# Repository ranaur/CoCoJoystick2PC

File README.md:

# CoCoJoystick2PC

Make a CoCo (Color Computer) Joystick a USB device (and use in your emulator) with an Arduino Leonardo!

The idea is to use a simple and cheap Arduino Leonardo to simulate a HID Gamepad that reads from a original Color Computer Joystick.

## Bill Of Materials

The Bill Of Materials should be minimal:

* An Arduino Leonardo or Compatible
* A DIN-6 female connector to insert the joystick - or two, if you want to handle two joysticks.
* A push button (to set the calibrate mode)
* Optional: pin switches (or you can wire directly if you don't want to configure the USB behavior)

If you buy an original Leonardo, it would cost around US$ 25. But it will be much cheaper (like less than half) if you buy a compatible board with ATMEGA32U4 controller.

## Subprojects

There are some subprojects (directories with .INO files) I did to test some features. They are not part of the main project, and are here just for educational (and backup) purposes:

* CoCoDetectJoystick: detects when the Joystick is inserted and removed
* Prototype: just a first prototype to test the circuit. Not Usable.
* Prototype2: a second prototype, a working one. The debouncing is simple (just a delay(100)), has calibration, but the code is a mess. It works, and the main ideas of the project are already there.
* CoCoJoystick2USB: the main project, this one is the real one. (not yet in the repository, sorry).

Since version 0.3 the project don't use HID-Project (2.8.2) anymore (but I'm grateful for the insights and idea for implementing the HID protocol!). To add it go in the Arduino IDE menu: Tools/Manage Libraries ... Search for HID-Project and install it.

## Files on Main project

Since the second prototype, things got a little bit more complex and organized. Lets describe the main classes/modules:

CoCoJoystick2USB.ino => main project file. Quite simple, because it instantiates all the classes that handles everything that is needed. The real job is done by CoCoJoystick class.

CoCoJoystick.cpp/.h => handles one Joystick. The setup() method defines which pins will be used for reading the joystick info (X Axis, Y Axis, Button 1 and Button 2) and the offset of the calibration data. The loop() method handle the reading of the pins and the delegation to a handler function. It also handles the calibration routines (startCalibration, centerCalibration and endCalibration) and loading/saving it to EEPROM. The calibration is done in two phases. First phase it read the maximum/minimum of the analog joystick (the user should move the stick as far as he can in all directions). The second phase tests for the center. The user cam move it slightly to handle any vibration of the stick. Or leave it in the center. If the stick goes back to any place of this region it will be considered as "center". The calibration data is saved on the EEPROM in a offset address.
	The reading of values are done by two classes. The stick (analog) is read by two AxisEvent instances (one for X and one for Y). The buttons are handled by two instances of ButtonEvent class.

\*Event Classes => While they are different classes, both share the same paradigm. Run setup() to configure parameters (i.e. pin number, tolecance, EEPROM Offset of calibration data ...) on the loop() routine of the microprocessor call the on\*() classes, that will handle reading, and, if necessary, call the first parameter, that is a callback function. Also, the on\*() methods can receive one pointer to pass to the callback function (Normally the event object itself, but it ca be anything), and the timer (optional). The timer parameter exist to call mills() just once and reuse the value through many calls in the loop() routine. Best use example is CoCoJoystick::loop().

AxisEvent.cpp/.h => Handles on axis. Reads the pin (0 to 1023) and normalize taking account of the calibration values. Handles the calibration state, aswell. The method onChanged() fires the callback if the value read from the sensor differs for more than the "tolerance" parameter. It handles the calibration routine aswell.

ButtonEvent.cpp/.h => Handles one button, with debounce. Has methods onPressed, onReleased, onPressedFor, onReleasedFor that calls the callback function on a button press (KEYDOWN), on a button release (KEYUP), after forMs miliseconds of the button press, and the same for the releade

Calibration.cpp/.h => the Calibration Objects encapsulates the real access to EEPROM, and the mapping from real values to adjusted (calibrated) values.

CoCoGamepadConfig.h => Abstract class that represents the interface of the events that can happen with a CoCo Gamepad could do. (press and release of the buttons, axis change).

# Usage

## Calibrate button
If using a spare button for CALIBRATION (#define CALIBRATION 2)
* If pressed, start calibration process. See "Calibration Process".
* If pressed for 10 seconds, reset the calibration to defaults.

If not using a spare button for CALIBRATION (#define CALIBRATION 1)
During the first 60 seconds after inserting the USB connector, if the user press the red button for 5 seconds, the calibration process starts.
	While it can be calibrated, the builtin led blinks continuously.
	When the calibration starts, it blinks once per second and gather the extremes.
	When you press the red button again, it blinks twice per second telling it is gathering the center region.
	When you press the red button, times out, it finishes the calibration.
	When the 60 seconds passes, it turns the led off.

## Calibration process

* Center Joystick and press the calibrate button
* Move the joystick to extremes: left right, up and down. Circle it a couple of times. Center it again.
* Press the red button
* Leave the joystick at the center or move very slightly (move the base of the joystick, not the stick), just to make the stick oscillate the center.
* Press the red button again
* At any moment pressing the black button cancel the calibration.
* If you stay more than 60 seconds and do not press the red button, the calibration cancels (timeout).

## Useful tips

### Get rid of: "note: #pragma message: Using default ASCII layout for keyboard modules" when compiling

This message is useful if you are programming a keyboard. But we are not. It is just annoying. To get rig of it:

Comment line 54 of ...\arduino\libraries\hid-project\src\keyboardlayouts\improvedkeylayouts.h

	#pragma message "Using default ASCII layout for keyboard modules"

to

	//#pragma message "Using default ASCII layout for keyboard modules"

# Tags

Git tags for the project

v0.1 -	First working version, one joystick, calibration.
v0.2 -	Fix: Now it appears as only one joystick.
	Less debug info.
	Detection Routines added. (needs extra wire shell of the on connector)
v0.3 - Now the HID report only what the joystick really have (2 axis and two buttons)
	Major refactor on calibration
v0.3.1 - More refactor on calibration. Timeout in 10 sec. Button now resets calibration after 3 secs. Black button cancels calibration.
v0.4 - General cleanup, speedup, optimizations, specially on calibration.
v0.5 - First version that handles two joysticks with one board. (if you don't want it, comment #define TWO_JOYSTICK in CoCoJoystick2PC.ino)
v0.6 - Enhancements when handling two joysticks. Now calibration start if the user press the button for 5 seconds in the first 60 seconds after inserting the device.
v0.6-BEETLE - version suitable to use in an Beetle Leonardo. BOM is only the [beetle board](https://www.aliexpress.com/item/1005003830541782.html), a DIN-6 Female Connector and wire to connect them. 

# TODO

## Next Steps

* Do/Test Single report USB

* Test it on ATTINY85
	- Use LUFA to handle USB?
* Automatic firing
	- use potentiometer for time
	- calibrate timing

## Waiting for the new board that works on breadboard
* Add a repeater on buttons
	- Add a potentiometer for speed (0-1023 ms) (>1000 => NO REPEAT)
	- Do it on buttons due lack of analog input: press button for repeat "save". Test average/minimum between presses. Long press cancel.

* Create config switches:
	* Red/Black reports as both buttons (for joysticks that has no secondary button) (3 secs press or when ping 6 is not connected)
	* Swap vertical axis (CP-400 mode)

* Create Switches: (A)
	- class SwitchEvent(nBits) {
		onChange()
		value()
	}

## Two Joysticks, one box
* Allow more than one joystick
	* with 2 joysticks report as two devices
		* On Gamepad Mode, report as one device, left Joy to the left axis control, right joy to right axis control, four buttons.
	* Make it Double: answer as two joysticks if just one joystick is connected
		(if detection is ok, answer always as two: if only one is connected, set the output to both.)

## Test Detection
	>> need to solder cables
	* Connect reset to output with diode and make a programable "reset"
	* detect which joysticks are present on setup and setup usb accordingly
	* when a joystick is connected/disconnectes, resets to redo the report
	* When just one joystick is connected use the single joystick as two joysticks
## Cosmetic changes
* Change the Joystick name from "Arduino Leonardo" to "CoCo Joystick(s)"
	- need to burn a new bootloader?
	- if so, disable "Leonardo" Serial Port

## Make a board to solder

## For future/next project
* Make it Bluetooth
* Make it XBox/Switch Control Compatible mode on Gamepad Mode?

## Pins Planning

 1 - *TX (not used)
 2 - *RX (not used)
 3 - Select (Joy 1)
 4 - Start (Joy 1)
 5 - Command Button (when pressed with joystick buttons ... thing happens)
		Red => Invert buttons, make both (or when does not detect the second button), 
		Black => Invert joysticks
		Y Max / Min => Swap Vertical
		select => Change mode (CoCo/NES/Atari/Gamepad)
		start =>
 6 - Joystick Detection (2nd)
 7 - Black Button (2nd)
 8 - Red Button (2nd)
 9 - Calibrate
10 - Joystick Detection
11 - Black Button
12 - Red Button
13 - *Not used (bad pin)
A0 - Axis X
A1 - Axis Y
A2 - Axis X (2nd)
A3 - Axis Y (2nd)
A4 - Turbo mode (potentiometer)
A5 - Free

# Sites

PluggableUSB and PluggableHID howto - arduino/Arduino Wiki
https://github-wiki-see.page/m/arduino/Arduino/wiki/PluggableUSB-and-PluggableHID-howto

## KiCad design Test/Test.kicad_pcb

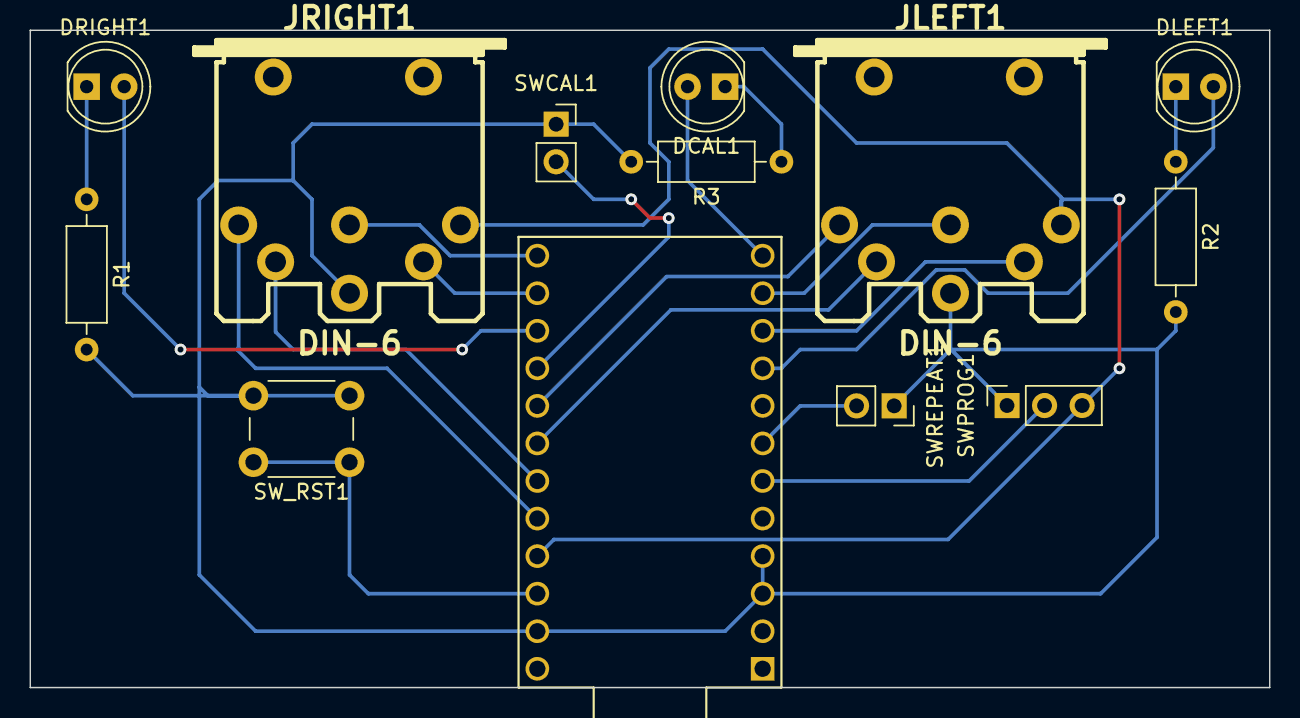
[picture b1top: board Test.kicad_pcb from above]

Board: 2 copper layers, 83.8 x 44.5 mm, 13 parts (0 on the bottom side), 20 nets.

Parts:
DCAL1: LED_Filled; LED_D5.0mm_FlatTop
DLEFT1: LED_Filled; LED_D5.0mm_FlatTop
DRIGHT1: LED_Filled; LED_D5.0mm_FlatTop
JLEFT1: DIN-6
JRIGHT1: DIN-6
R1, R2, R3: R; R_Axial_DIN0207_L6.3mm_D2.5mm_P10.16mm_Horizontal
SWCAL1: SW_Push; PinSocket_1x02_P2.54mm_Vertical
SWPROG1: SW_SPDT; PinSocket_1x03_P2.54mm_Vertical
SWREPEAT1: SW_Push; PinSocket_1x02_P2.54mm_Vertical
SW_RST1: SW_Push; SW_PUSH_6mm_H5mm
U1: ProMicro

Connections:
5V: JLEFT1.5, JRIGHT1.5, SWPROG1.3 (C), U1.21 (VCC)
Axis X L: JLEFT1.1, U1.17 (F7)
Axis X R: JRIGHT1.1, U1.20 (F4)
Axis Y L: JLEFT1.2, U1.18 (F6)
Axis Y R: JRIGHT1.2, U1.19 (F5)
BLACK L: JLEFT1.6, U1.11 (B4)
BLACK R: JRIGHT1.6, U1.13 (B6)
DCAL: DCAL1.2 (A), U1.12 (B5)
DLEFT: DLEFT1.2 (A), U1.9 (D7)
DRIGHT: DRIGHT1.2 (A), U1.15 (B3)
GND: JLEFT1.3, JRIGHT1.3, R1.2, R2.2, R3.2, SWCAL1.1, SWPROG1.1 (A), SWREPEAT1.1, SW_RST1.2, U1.3 (GND), U1.4 (GND), U1.23 (GND)
unnamed: DCAL1.1 (K), R3.1
unnamed: DLEFT1.1 (K), R2.1
unnamed: DRIGHT1.1 (K), R1.1
unnamed: SW_RST1.1, U1.22 (RST)
RED L: JLEFT1.4, U1.10 (E6)
RED R: JRIGHT1.4, U1.14 (B2)
SWCAL: SWCAL1.2, U1.16 (B1)
SWPROG: SWPROG1.2 (B), U1.6 (SCL)
SWREPEAT: SWREPEAT1.2, U1.7 (D4)

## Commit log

2022-03-17 First version, import from the directories. No Main program yet.
2022-03-18 First working version.
2022-03-19 Added tags section in documentation
2022-03-19 Removed Debug information
2022-03-19 Added joystick detection
2022-03-19 Fix multiple appearances of joystick (using now Gamepad, instead of Gamepad1)
2022-03-19 removed debug info (or left in #ifdef DEBUG)
2022-03-21 Changed HID Descriptor to a cleaner output (WIP)
2022-03-21 Changed HID Descriptor to report only two axes and two buttons
2022-03-22 Major EEPROM routines refactor. DUBUG protected by #ifdef, calibration routines refactored too
2022-03-23 Allowed to pool last value, and general cleanup
2022-03-23 Added actuated on *For routined to suporess multiple calls after the time
2022-03-23 Event handlers are now static methods of class. Added calibration reset on black button and timeout.
2022-03-23 mend
    Event handlers are now static methods of class. Added calibration cancel on black button and timeout.
2022-03-23 FIrst version needed for calibration timeout.
2022-03-23 Protected debug info
2022-03-23 Refactor classes from *GamePadConfig to CoCoJoystickEvent
2022-03-23 Refactor *GamepadConfig to CoCoJoystick
2022-03-23 Ask limit from CoCoJoystickEvent
2022-03-24 Renamed the project to avoid name clash with a previous CoCoJoystick2USB project
2022-04-02 Add optional joystick detection by #define
2022-04-04 Two joystick support
2022-04-16 More USB HID connectors
2022-04-16 PCB Prototype (not tested, probably won't work)
2022-04-16 First version os state button (not tested)
2022-04-16 Recatored debugging functions
2022-04-16 Refactored debugging functions
2022-04-16 Added swap-joysticks button
2022-04-20 Fix pressFor bug during start
2022-04-20 Added blinker class
2022-04-20 Board configuration should be in the INO file
2022-04-20 mend
2022-04-20 Setted Beetle USB support
2022-04-20 Callback support on startCalibrate
2022-04-21 Leonardo BEETLE Board support
2022-05-10 Initial Gerber (not tested)
2022-05-14 control chenges so won't report the same report twice
